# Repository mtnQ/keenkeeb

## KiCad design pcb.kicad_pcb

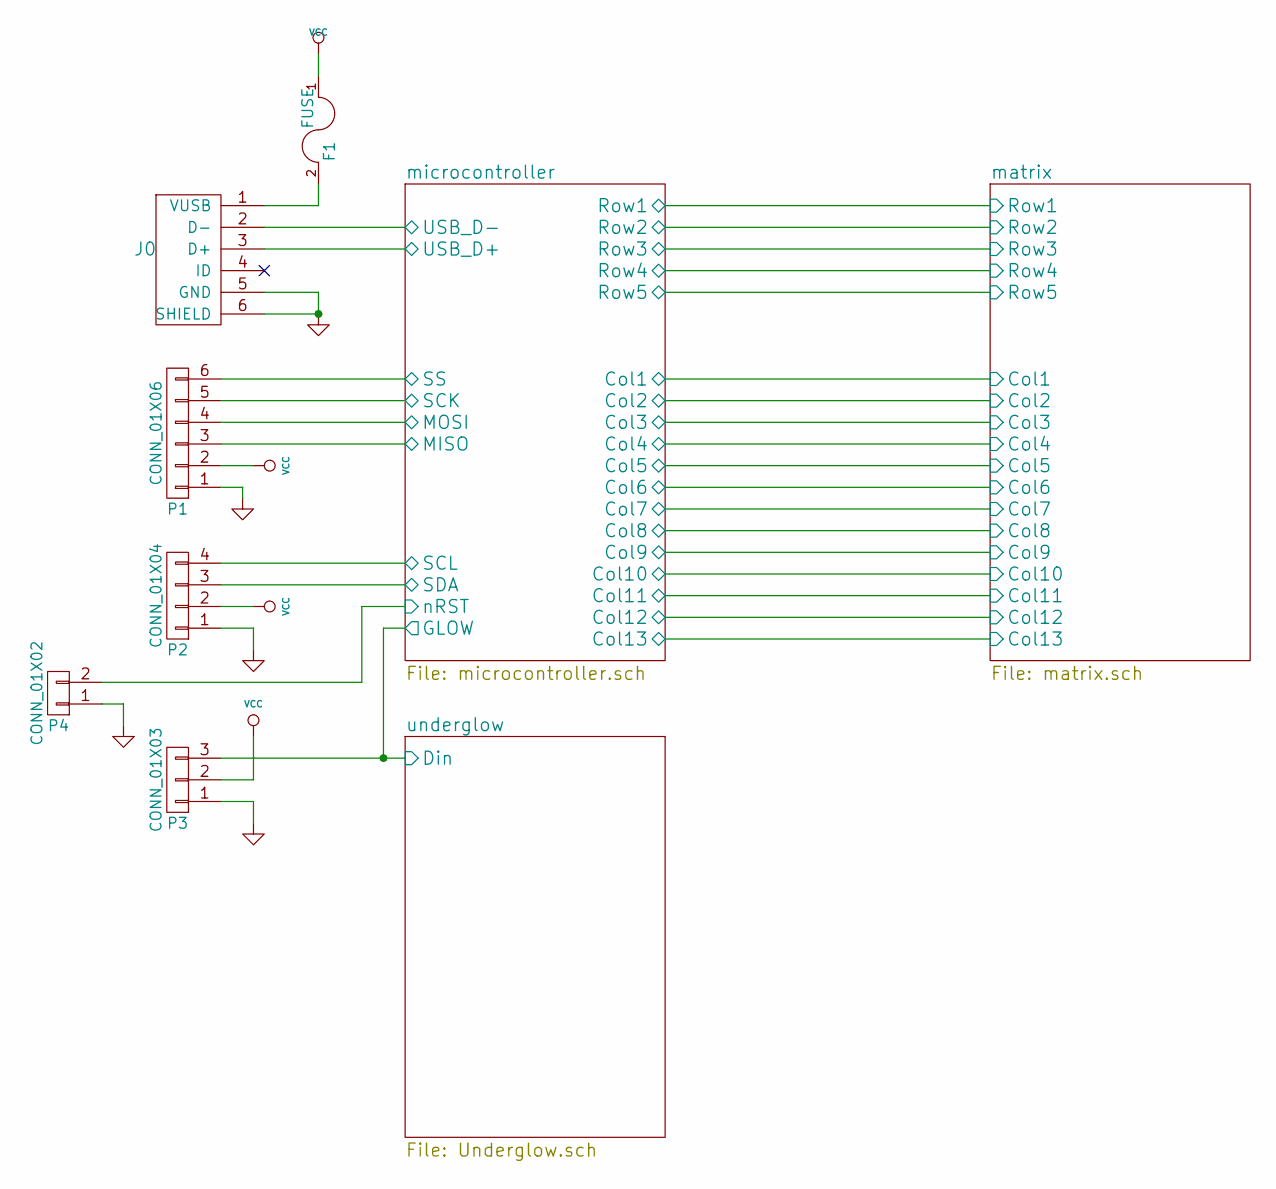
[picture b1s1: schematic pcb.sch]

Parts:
F1: FUSE; LED_0805
J0: USB_mini_micro_B; USB_miniB_hirose_5S8
P1: CONN_01X06; Pin_Header_Straight_1x06_Pitch2.54mm
P2: CONN_01X04; Pin_Header_Straight_1x04_Pitch2.54mm
P3: CONN_01X03; Pin_Header_Straight_1x03_Pitch2.54mm
P4: CONN_01X02; Pin_Header_Straight_1x02_Pitch2.54mm

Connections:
/microcontroller/MISO: P1.3; also elsewhere on the board
/microcontroller/MOSI: P1.4; also elsewhere on the board
/microcontroller/SCK: P1.5; also elsewhere on the board
/microcontroller/SCL: P2.4; also elsewhere on the board
/microcontroller/SDA: P2.3; also elsewhere on the board
/microcontroller/SS: P1.6; also elsewhere on the board
/microcontroller/USB_D+: J0.3 (D+); also elsewhere on the board
/microcontroller/USB_D-: J0.2 (D-); also elsewhere on the board
/underglow/Din: P3.3; also elsewhere on the board
unnamed: F1.2, J0.1 (VUSB)

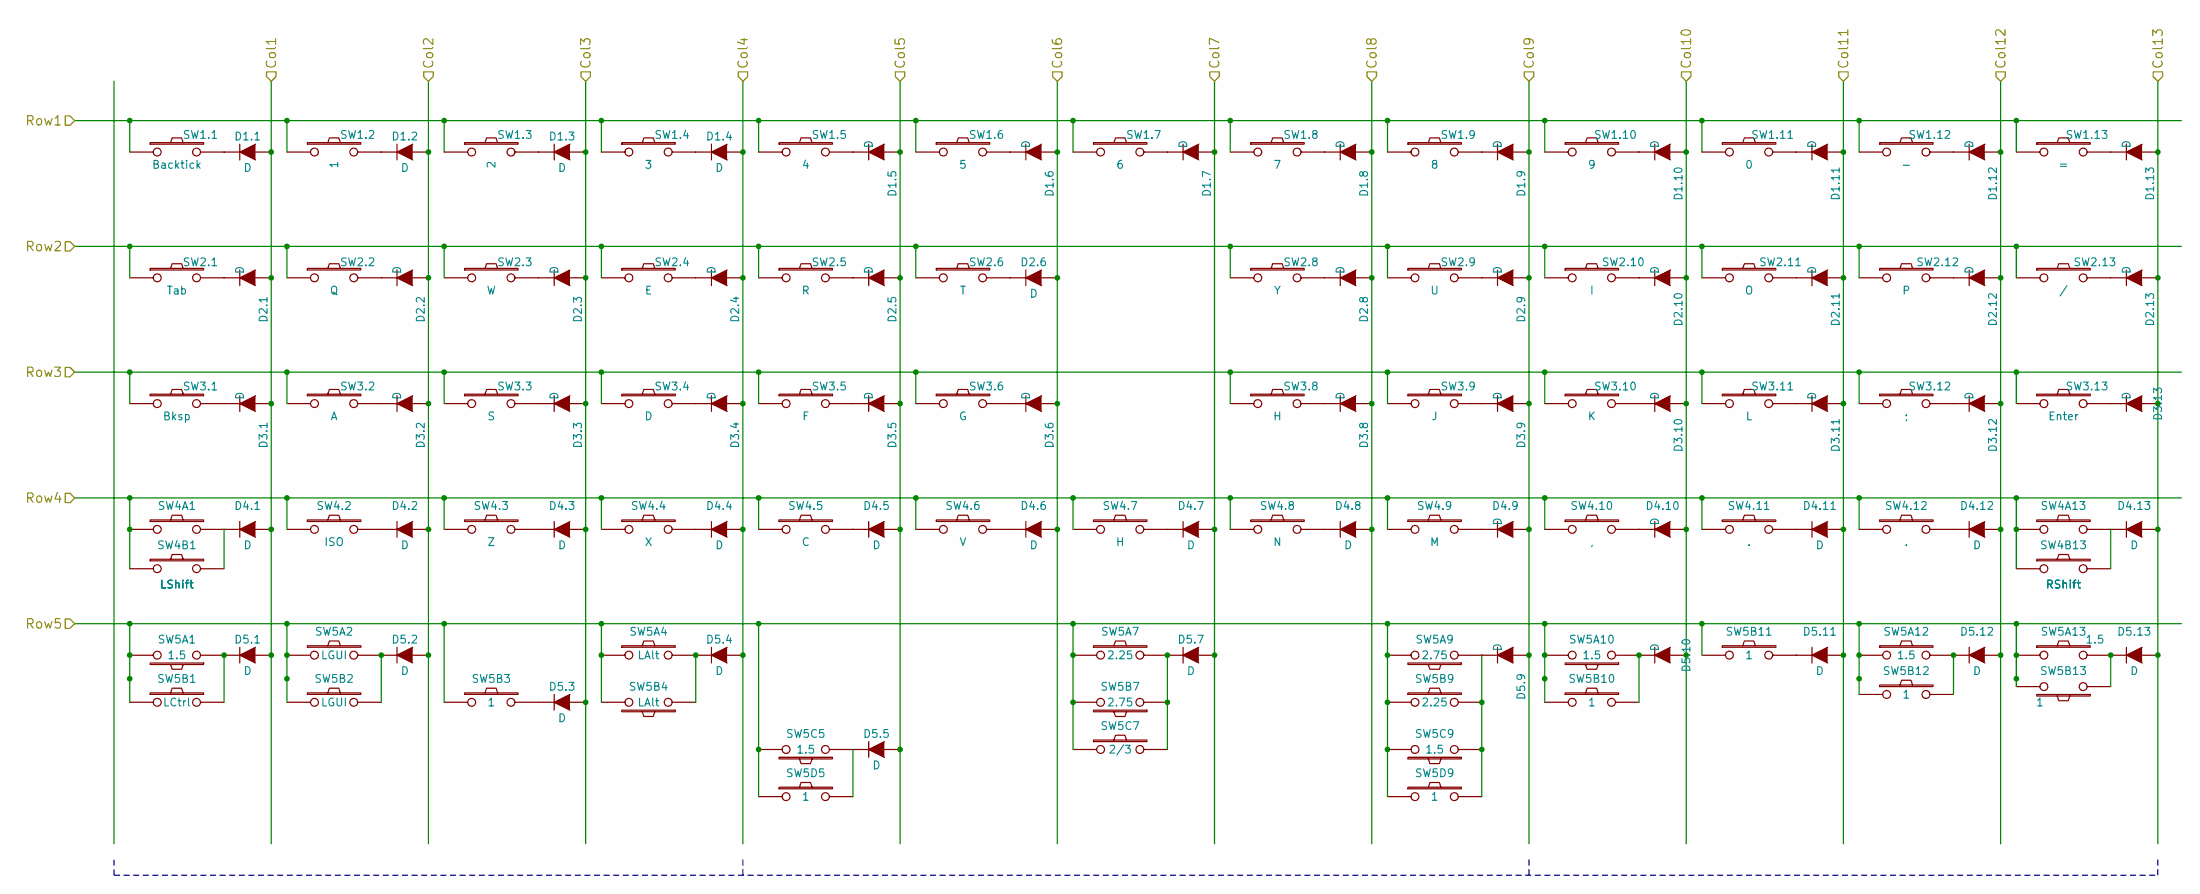
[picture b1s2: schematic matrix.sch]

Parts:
D1.1, D1.2, D1.3, D1.4, D1.5, D1.6, D1.7, D1.8, D1.9, D1.10, D1.11, D1.12, D1.13, D2.1, D2.2, D2.3, D2.4, D2.5, D2.6, D2.8, D2.9, D2.10, D2.11, D2.12, D2.13, D3.1, D3.2, D3.3, D3.4, D3.5, D3.6, D3.8, D3.9, D3.10, D3.11, D3.12, D3.13, D4.1, D4.2, D4.3, D4.4, D4.5, D4.6, D4.7, D4.8, D4.9, D4.10, D4.11, D4.12, D4.13, D5.1, D5.2, D5.3, D5.4, D5.5, D5.7, D5.10, D5.11, D5.12, D5.13: D; D_SOD-323_HandSoldering
SW1.1: Backtick; Mx_Alps_100
SW1.2, SW5B3, SW5B10, SW5B11, SW5B12, SW5B13, SW5D5, SW5D9: 1; Mx_Alps_100
SW1.3: 2; Mx_Alps_100
SW1.4: 3; Mx_Alps_100
SW1.5: 4; Mx_Alps_100
SW1.6: 5; Mx_Alps_100
SW1.7: 6; Mx_Alps_100
SW1.8: 7; Mx_Alps_100
SW1.9: 8; Mx_Alps_100
SW1.10: 9; Mx_Alps_100
SW1.11: 0; Mx_Alps_100
SW1.12: -; Mx_Alps_100
SW1.13: =; Mx_Alps_100
SW2.1: Tab; Mx_Alps_150
SW2.2: Q; Mx_Alps_100
SW2.3: W; Mx_Alps_100
SW2.4: E; Mx_Alps_100
SW2.5: R; Mx_Alps_100
SW2.6: T; Mx_Alps_100
SW2.8: Y; Mx_Alps_100
SW2.9: U; Mx_Alps_100
SW2.10: I; Mx_Alps_100
SW2.11: O; Mx_Alps_100
SW2.12: P; Mx_Alps_100
SW2.13: /; Mx_Alps_150
SW3.1: Bksp; Mx_Alps_150
SW3.2: A; Mx_Alps_100
SW3.3: S; Mx_Alps_100
SW3.4: D; Mx_Alps_100
SW3.5: F; Mx_Alps_100
SW3.6: G; Mx_Alps_100
SW3.8, SW4.7: H; Mx_Alps_100
SW3.9: J; Mx_Alps_100
SW3.10: K; Mx_Alps_100
SW3.11: L; Mx_Alps_100
SW3.12: ;; Mx_Alps_100
SW3.13: Enter; Mx_Alps_150
SW4.2: ISO; Mx_Alps_100
SW4.3: Z; Mx_Alps_100
SW4.4: X; Mx_Alps_100
SW4.5: C; Mx_Alps_100
SW4.6: V; Mx_Alps_100
SW4.8: N; Mx_Alps_100
SW4.9: M; Mx_Alps_100
SW4.10: ,; Mx_Alps_100
SW4.11, SW4.12: .; Mx_Alps_100
SW4A1: LShift; Mx_Alps_200
SW4A13: RShift; Mx_Alps_200
SW4B1: LShift; Mx_Alps_100
SW4B13: RShift; Mx_Alps_100
SW5A1, SW5A10, SW5A13, SW5C5, SW5C9: 1.5; Mx_Alps_150
SW5A2, SW5B2: LGUI; Mx_Alps_100
SW5A4: LAlt; Mx_Alps_150
SW5A7, SW5B9: 2.25; Mx_Alps_225
SW5A9, SW5B7: 2.75; Mx_Alps_275
SW5A12: 1.5; Mx_Alps_100
SW5B1: LCtrl; Mx_Alps_100
SW5B4: LAlt; Mx_Alps_100
SW5C7: 2/3; Mx_Alps_200

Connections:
/matrix/Col1: D1.1.2 (A), D2.1.2 (A), D3.1.2 (A), D4.1.2 (A), D5.1.2 (A); also elsewhere on the board
/matrix/Col2: D1.2.2 (A), D2.2.2 (A), D3.2.2 (A), D4.2.2 (A), D5.2.2 (A); also elsewhere on the board
/matrix/Col3: D1.3.2 (A), D2.3.2 (A), D3.3.2 (A), D4.3.2 (A), D5.3.2 (A); also elsewhere on the board
/matrix/Col4: D1.4.2 (A), D2.4.2 (A), D3.4.2 (A), D4.4.2 (A), D5.4.2 (A); also elsewhere on the board
/matrix/Col5: D1.5.2 (A), D2.5.2 (A), D3.5.2 (A), D4.5.2 (A), D5.5.2 (A); also elsewhere on the board
/matrix/Col6: D1.6.2 (A), D2.6.2 (A), D3.6.2 (A), D4.6.2 (A); also elsewhere on the board
/matrix/Col8: D1.8.2 (A), D2.8.2 (A), D3.8.2 (A), D4.8.2 (A); also elsewhere on the board
/matrix/Col10: D1.10.2 (A), D2.10.2 (A), D3.10.2 (A), D4.10.2 (A), D5.10.2 (A); also elsewhere on the board
/matrix/Col11: D1.11.2 (A), D2.11.2 (A), D3.11.2 (A), D4.11.2 (A), D5.11.2 (A); also elsewhere on the board
/matrix/Col12: D1.12.2 (A), D2.12.2 (A), D3.12.2 (A), D4.12.2 (A), D5.12.2 (A); also elsewhere on the board
/matrix/Col13: D1.13.2 (A), D2.13.2 (A), D3.13.2 (A), D4.13.2 (A), D5.13.2 (A); also elsewhere on the board
/matrix/Row1: SW1.1.1, SW1.2.1, SW1.3.1, SW1.4.1, SW1.5.1, SW1.6.1, SW1.7.1, SW1.8.1, SW1.9.1, SW1.10.1, SW1.11.1, SW1.12.1, SW1.13.1; also elsewhere on the board
/matrix/Row2: SW2.1.1, SW2.2.1, SW2.3.1, SW2.4.1, SW2.5.1, SW2.6.1, SW2.8.1, SW2.9.1, SW2.10.1, SW2.11.1, SW2.12.1, SW2.13.1; also elsewhere on the board
/matrix/Row3: SW3.1.1, SW3.2.1, SW3.3.1, SW3.4.1, SW3.5.1, SW3.6.1, SW3.8.1, SW3.9.1, SW3.10.1, SW3.11.1, SW3.12.1, SW3.13.1; also elsewhere on the board
/matrix/Row4: SW4.2.1, SW4.3.1, SW4.4.1, SW4.5.1, SW4.6.1, SW4.7.1, SW4.8.1, SW4.9.1, SW4.10.1, SW4.11.1, SW4.12.1, SW4A1.1, SW4A13.1, SW4B1.1, SW4B13.1; also elsewhere on the board
/matrix/Row5: SW5A1.2, SW5A2.1, SW5A4.1, SW5A7.1, SW5A9.2, SW5A10.2, SW5A12.1, SW5A13.1, SW5B1.1, SW5B2.1, SW5B3.1, SW5B4.2, SW5B7.2, SW5B9.1, SW5B10.1, SW5B11.1, SW5B12.1, SW5B13.2, SW5C5.2, SW5C7.1, SW5C9.2, SW5D5.1, SW5D9.1; also elsewhere on the board
unnamed: D1.1.1 (K), SW1.1.2
unnamed: D1.2.1 (K), SW1.2.2
unnamed: D1.3.1 (K), SW1.3.2
unnamed: D1.4.1 (K), SW1.4.2
unnamed: D1.5.1 (K), SW1.5.2
unnamed: D1.6.1 (K), SW1.6.2
unnamed: D1.7.1 (K), SW1.7.2
unnamed: D1.8.1 (K), SW1.8.2
unnamed: D1.9.1 (K), SW1.9.2
unnamed: D1.10.1 (K), SW1.10.2
unnamed: D1.11.1 (K), SW1.11.2
unnamed: D1.12.1 (K), SW1.12.2
unnamed: D1.13.1 (K), SW1.13.2
unnamed: D2.1.1 (K), SW2.1.2
unnamed: D2.2.1 (K), SW2.2.2
unnamed: D2.3.1 (K), SW2.3.2
unnamed: D2.4.1 (K), SW2.4.2
unnamed: D2.5.1 (K), SW2.5.2
unnamed: D2.6.1 (K), SW2.6.2
unnamed: D2.8.1 (K), SW2.8.2
unnamed: D2.9.1 (K), SW2.9.2
unnamed: D2.10.1 (K), SW2.10.2
unnamed: D2.11.1 (K), SW2.11.2
unnamed: D2.12.1 (K), SW2.12.2
unnamed: D2.13.1 (K), SW2.13.2
unnamed: D3.1.1 (K), SW3.1.2
unnamed: D3.2.1 (K), SW3.2.2
unnamed: D3.3.1 (K), SW3.3.2
unnamed: D3.4.1 (K), SW3.4.2
unnamed: D3.5.1 (K), SW3.5.2
unnamed: D3.6.1 (K), SW3.6.2
unnamed: D3.8.1 (K), SW3.8.2
unnamed: D3.9.1 (K), SW3.9.2
unnamed: D3.10.1 (K), SW3.10.2
unnamed: D3.11.1 (K), SW3.11.2
unnamed: D3.12.1 (K), SW3.12.2
unnamed: D3.13.1 (K), SW3.13.2
unnamed: D4.1.1 (K), SW4A1.2, SW4B1.2
unnamed: D4.2.1 (K), SW4.2.2
unnamed: D4.3.1 (K), SW4.3.2
unnamed: D4.4.1 (K), SW4.4.2
unnamed: D4.5.1 (K), SW4.5.2
unnamed: D4.6.1 (K), SW4.6.2
unnamed: D4.7.1 (K), SW4.7.2
unnamed: D4.8.1 (K), SW4.8.2
unnamed: D4.9.1 (K), SW4.9.2
unnamed: D4.10.1 (K), SW4.10.2
unnamed: D4.11.1 (K), SW4.11.2
unnamed: D4.12.1 (K), SW4.12.2
unnamed: D4.13.1 (K), SW4A13.2, SW4B13.2
unnamed: D5.1.1 (K), SW5A1.1, SW5B1.2
unnamed: D5.2.1 (K), SW5A2.2, SW5B2.2
unnamed: D5.3.1 (K), SW5B3.2
unnamed: D5.4.1 (K), SW5A4.2, SW5B4.1
unnamed: D5.5.1 (K), SW5C5.1, SW5D5.2
unnamed: D5.10.1 (K), SW5A10.1, SW5B10.2
unnamed: D5.11.1 (K), SW5B11.2
unnamed: D5.12.1 (K), SW5A12.2, SW5B12.2
unnamed: D5.13.1 (K), SW5A13.2, SW5B13.1

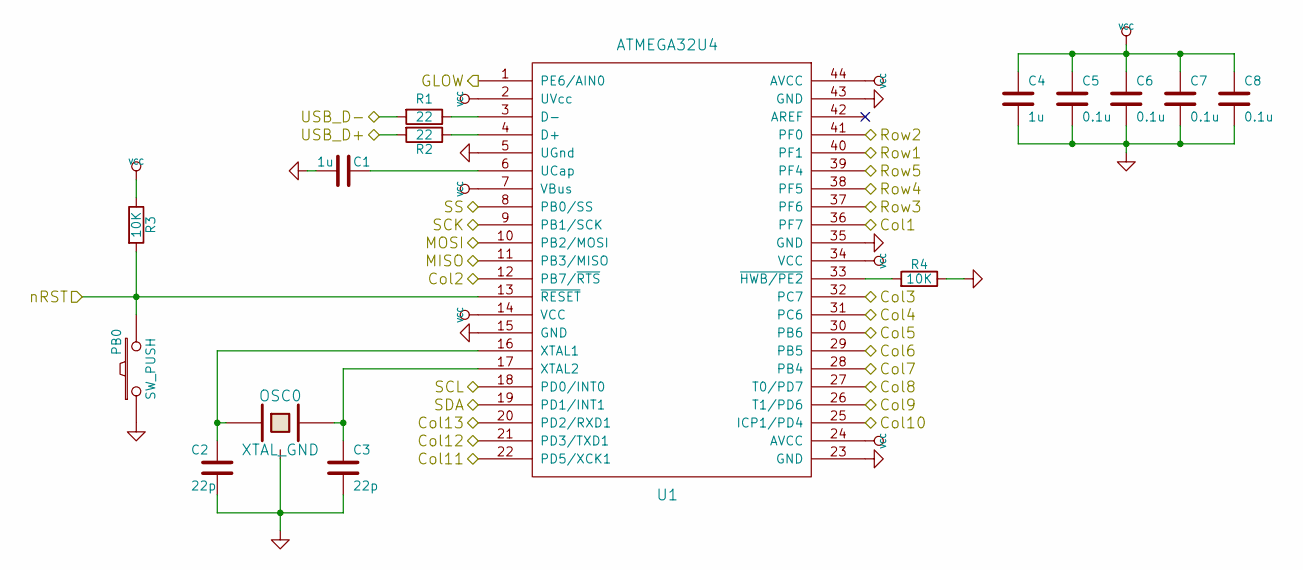
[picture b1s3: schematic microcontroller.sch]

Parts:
C0, C3: 1u; C_0805
C1, C2: 22p; C_0805
C4, C5, C6, C7: 0.1u; C_0805
OSC0: XTAL_GND; OSC_EpsonFA238_SMD
PB0: SW_PUSH; SW_SPST_SKQG
R0, R3: 10K; R_0805
R1, R2: 22; R_0805
U1: ATMEGA32U4; TQFP-44_10x10mm_Pitch0.8mm

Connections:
/matrix/Col1: U1.36 (PF7); also elsewhere on the board
/matrix/Col2: U1.12 (PB7/~RTS); also elsewhere on the board
/matrix/Col3: U1.32 (PC7); also elsewhere on the board
/matrix/Col4: U1.31 (PC6); also elsewhere on the board
/matrix/Col5: U1.30 (PB6); also elsewhere on the board
/matrix/Col6: U1.29 (PB5); also elsewhere on the board
/matrix/Col8: U1.27 (T0/PD7); also elsewhere on the board
/matrix/Col10: U1.25 (ICP1/PD4); also elsewhere on the board
/matrix/Col11: U1.22 (PD5/XCK1); also elsewhere on the board
/matrix/Col12: U1.21 (PD3/TXD1); also elsewhere on the board
/matrix/Col13: U1.20 (PD2/RXD1); also elsewhere on the board
/matrix/Row1: U1.40 (PF1); also elsewhere on the board
/matrix/Row2: U1.41 (PF0); also elsewhere on the board
/matrix/Row3: U1.37 (PF6); also elsewhere on the board
/matrix/Row4: U1.38 (PF5); also elsewhere on the board
/matrix/Row5: U1.39 (PF4); also elsewhere on the board
/microcontroller/MISO: U1.11 (PB3/MISO); also elsewhere on the board
/microcontroller/MOSI: U1.10 (PB2/MOSI); also elsewhere on the board
/microcontroller/SCK: U1.9 (PB1/SCK); also elsewhere on the board
/microcontroller/SCL: U1.18 (PD0/INT0); also elsewhere on the board
/microcontroller/SDA: U1.19 (PD1/INT1); also elsewhere on the board
/microcontroller/SS: U1.8 (PB0/SS); also elsewhere on the board
/microcontroller/USB_D+: R2.2; also elsewhere on the board
/microcontroller/USB_D-: R1.2; also elsewhere on the board
/underglow/Din: U1.1 (PE6/AIN0); also elsewhere on the board
unnamed: R1.1, U1.3 (D-)
unnamed: R2.1, U1.4 (D+)

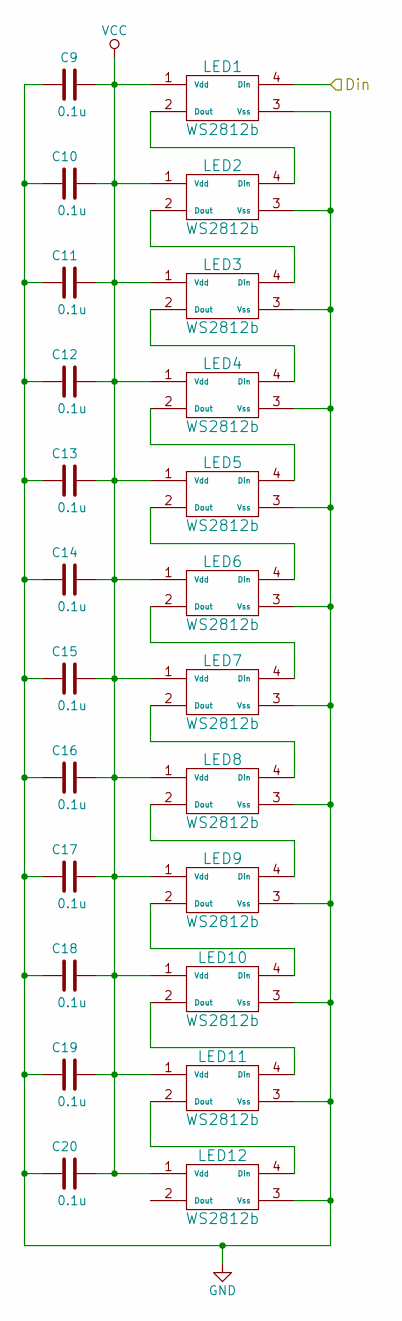
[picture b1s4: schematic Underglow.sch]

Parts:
C9, C10, C11, C12, C13, C14, C15, C16, C17, C18, C19, C20: 0.1u; C_0805
LED1, LED2, LED3, LED4, LED5, LED6, LED7, LED8, LED9, LED10, LED11, LED12: WS2812b; LED_WS2812B-PLCC4

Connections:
/underglow/Din: LED1.4 (Din); also elsewhere on the board
unnamed: LED1.2 (Dout), LED2.4 (Din)
unnamed: LED2.2 (Dout), LED3.4 (Din)
unnamed: LED3.2 (Dout), LED4.4 (Din)
unnamed: LED4.2 (Dout), LED5.4 (Din)
unnamed: LED5.2 (Dout), LED6.4 (Din)
unnamed: LED6.2 (Dout), LED7.4 (Din)
unnamed: LED7.2 (Dout), LED8.4 (Din)
unnamed: LED8.2 (Dout), LED9.4 (Din)
unnamed: LED10.2 (Dout), LED11.4 (Din)
unnamed: LED9.2 (Dout), LED10.4 (Din)
unnamed: LED11.2 (Dout), LED12.4 (Din)

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
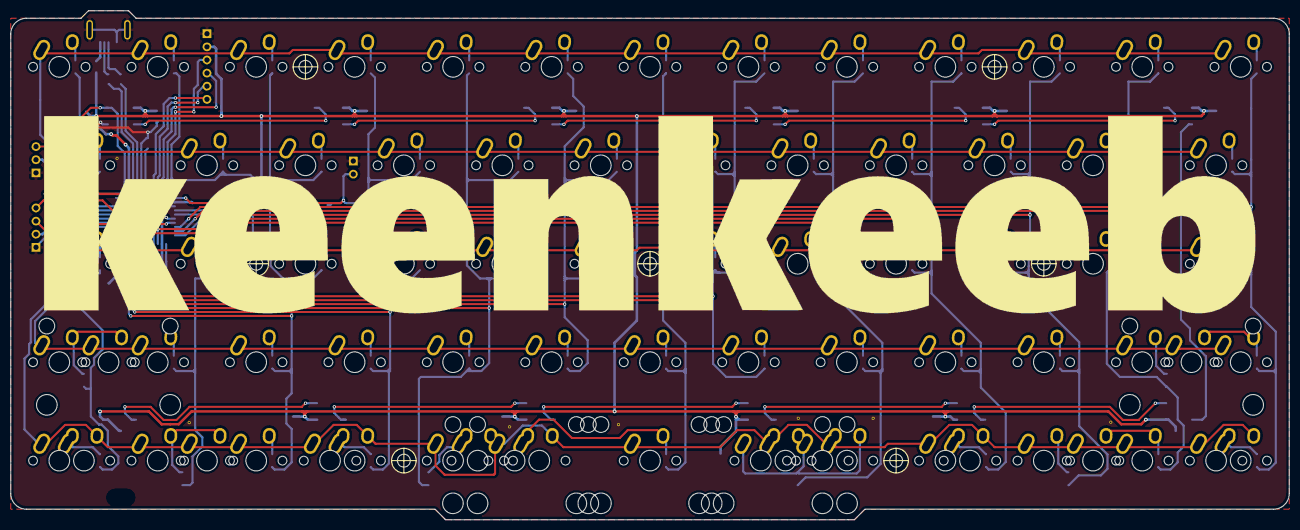
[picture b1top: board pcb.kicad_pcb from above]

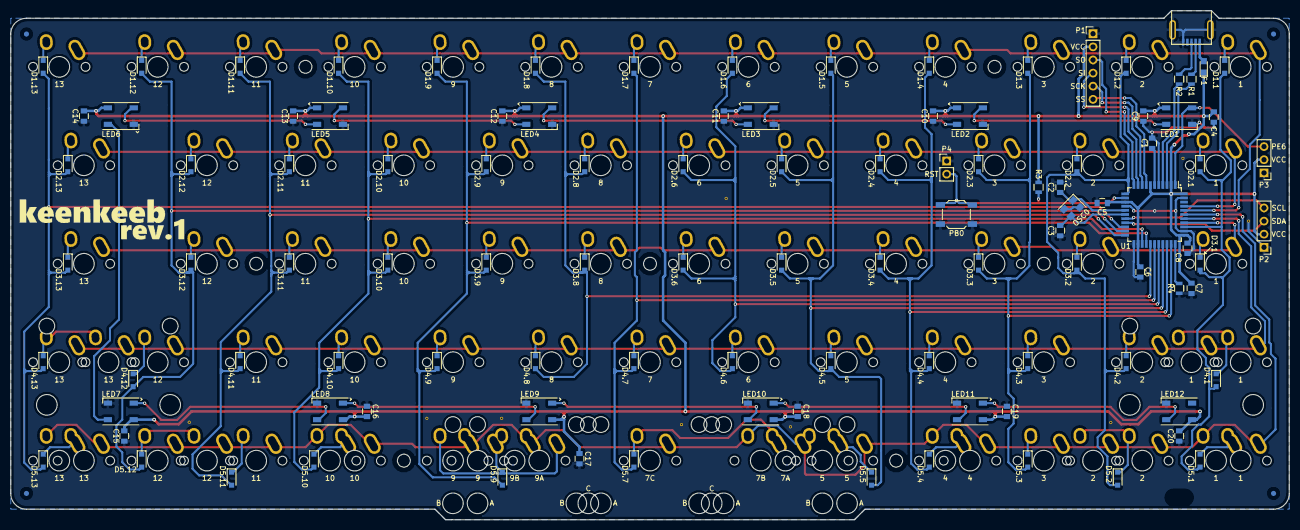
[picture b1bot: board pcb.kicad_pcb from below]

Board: 2 copper layers, 247.4 x 98.5 mm, 203 parts (106 on the bottom side), 109 nets.

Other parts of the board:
C8: 0.1u; C_0805
D5.9: D; D_SOD-323_HandSoldering
FIDUCIAL: Fiducial_1mm_Dia_2.54mm_Outer_CopperBottom
FIDUCIAL#2, FIDUCIAL#3, FIDUCIAL#4: Fiducial_1mm_Dia_2.54mm_Outer_CopperBottom
G1: LOGO; keenkeeb-graphic
Hole3, Hole3#2, Hole3#3, Hole3#4, Hole3#5, Hole3#6, Hole3#7: M2; Mount_M2_NP
Hole4: M2; Mount_M2_Oval_NP
R4: 10K; R_0805
Stitch1, Stitch2, Stitch3, Stitch4, Stitch4#2, Stitch5, Stitch6, Stitch6#2, Stitch7: Via-0.6mm

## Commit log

2017-05-11 Added license file.
    Added LICENSE, which holds CC BY-SA licensing.
2017-05-11 Added project files.
    Added KiCad design files for schematic and layout.
2017-05-11 Added resource files.
    Added resources/ which holds the json files for KLE and an image of the
    available layouts.
2017-05-12 License changed to GNU GPL v3.0
2017-05-13 Branch for finalizing the board.
    TODO:
    Swap to smaller components, finalize pads
    Added footprints.pretty
    Add RGB underglow
    Added schematic library (keenkeeb.lib/dcm)
    Remove SPI header (?)
2017-05-16 ARR GEE BEE!!!
    Added pads for WS2812B underglow - connected to pin 11.
    Rerouted some connections.
2017-05-16 Added render of PCB.
2017-05-17 Added 0.1uF caps to LEDs
    Added capacitors from Vcc to GND for WS2812s
    Also changed some references
2017-05-21 Moved some of the footprints around.
2017-05-21 Created plans for rev. 1 of the PCB
    Will support many more layouts (100 by my math)
    Will need to add 2 more WS2812B LEDs to the board and move the micro
    where the 8th LED was.
2017-05-21 Updated layout image and JSON.
2017-05-22 Added footprints for platemount MX switches
    Removed holes needed by PCB-mount switches, so the board doesn't look
    like it could be snapped over your knee. Also, gives more space for
    traces.
2017-05-22 Begun work for rev 1 layout, which supports ortholinear rows 2 and 3.
    Converted all switches to use platemount footprint. Added additional
    set of switches to row 3 for a completely ortholinear layout.
2017-05-22 Ortholinear switch footprints added to row 2.
2017-05-23 Added footprints for 2+ unit keys without PCB stabilizer holes.
    2u, 2.25u, and 2.75u footprints added that have no holes for PCB-mounted
    stabilizer. Will use platemount stabilizer (cherry or costar)
2017-05-23 Added a bunch of additional switches for layouts
2017-05-24 All switch columns wired.
    Wired all switches in a column together and dropped the 10 existing
    WS2812Bs in place. Need to connect everything to controller.
2017-05-25 Updated rev 1 layout resources.
2017-05-25 About half of rows/columns connected to microcontroller.
2017-06-02 Focusing efforts on one main layout (semi-ortho), so that PCB-mounted and Alps components can be supported
    Updated keenkeeb-reb1.png with new layout.
    Started removing footprints and adding new spacebar footprints.
2017-06-02 Updated JSON to match PNG
2017-06-02 Updated readme.
2017-06-16 Started to layout with MX/Alps footprints
    Added footprints that support Cherry MX and Alps switches.
    Started to layout the board with new footprints. Will support PCB
    mounted switches/stabs.
2017-06-23 Connected most of the components on the board
    TODO:
    Replace P1 with 1x6 header for SPI, Vcc, GND
    Add test pads
2017-07-06 More progress on PCB
    Cleaned up silkscreen layers
    Updated switch footprints to remove front layer and hide reference on
    back layer
    Moved references on back layer
    Moved bottom mounting holes on PCB
    Cleaned up matrix schematic
2017-07-06 Added new graphic for back side of PCB
2017-07-06 Added renders of PCB to output/ directory
2017-07-06 Removed old MX-only footprints; Added mini USB footprint
    Need to use added mini USB footprint instead of current one (which looks
    at my KiCad directory)
2017-07-10 Added labeling to R5 stabs.
    Added A, B, C labels to stabilizer holes and associated switch holes.
2017-07-14 Cleaned up
    Automerged traces and removed redundant holes.
2017-07-15 Reduced font thickness on PCB
2017-07-15 Updated mounting holes to be non-plated
2017-07-15 Cleaned up tracks
    Automatic cleanup of tracks
2017-07-15 Updated USB footprint and added mounting holes
    Updated mini USB to use included footprint.
    Added two new mounting holes under bottom row of board.
2017-08-09 Shifted locations of vias for WS2812/Capacitors and shifted a couple traces
2017-08-09 Moved references for underglow LEDs so that they are visible when WS2812s are installed
2017-08-12 Fixed annular rings for vias
    Passed FreeDHM test
2017-08-16 Added fiducials, changed plot outputs for freedfm
    FreeDFM: Add edge layers on all plots
2017-08-17 Slight fixes to some silkscreen text
2018-04-05 Updated .gitignore
    Added *.zip and *.tar.gz
2018-04-05 Adjusted mounting holes and edge cuts
    Adjusted positions of all but center mounting hole.
    All mounting holes are now circular instead of oblong.
    Increased clearance around bottom-row stabilizers to (hopefully) improve
    manufacturing.
2018-04-06 Added positions of new mounting holes
    Relative to center hole
